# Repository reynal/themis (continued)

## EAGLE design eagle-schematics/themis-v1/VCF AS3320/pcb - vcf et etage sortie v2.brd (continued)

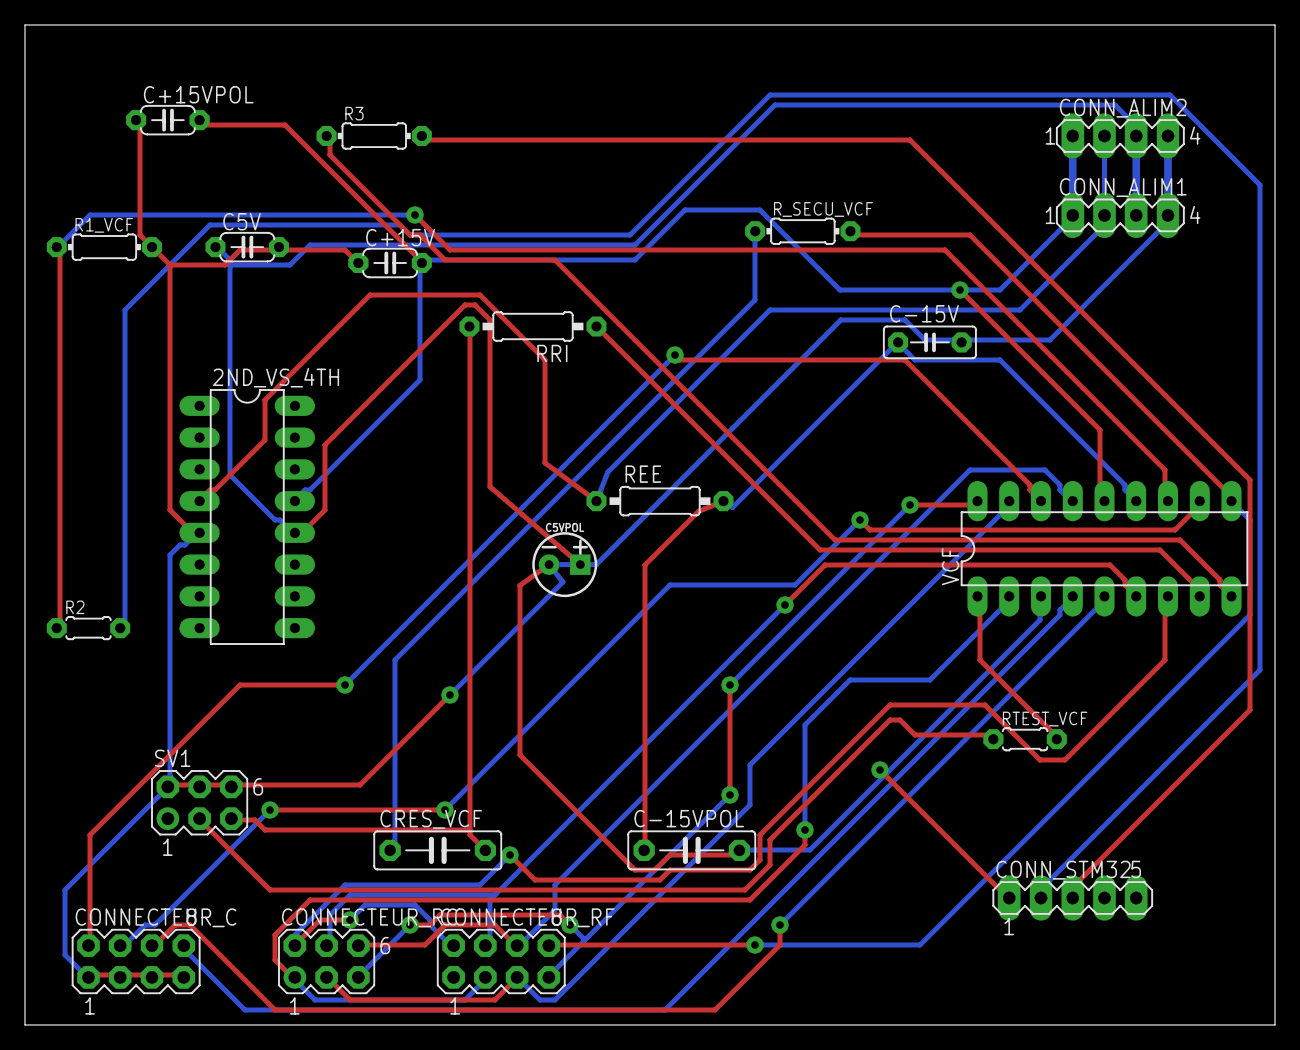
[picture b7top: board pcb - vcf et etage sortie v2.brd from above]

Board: 2 copper layers, 100.0 x 80.0 mm, 23 parts (0 on the bottom side), 25 nets.
